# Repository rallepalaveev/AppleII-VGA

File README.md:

# Apple II VGA Card

This project is a VGA card for Apple II computers to ouput a crisp RGB signal to a
VGA monitor instead of having to rely on the composite output. This is accomplished
by snooping the 6502 bus and creating a shadow copy of the video memory within a
Raspberry Pi Pico, then processing the raw video memory contents to output a "perfect"
signal.

    +------+                +-----+      +-----------+
    | 6502 |________________| RAM |______| Composite | 
    | CPU  |  System   \    +-----+      | Video Gen |
    +------+   Bus     |                 +-----------+
                       |    +-----------+
                       \____| Raspberry |_________________\
                            |  Pi Pico  |   640x480 VGA   /
                            +-----------+

These features are currently supported:
 * Generates a 640x480@60 VGA signal with 3 bits per color channel using resistor DACs
 * Text mode (monochrome)
 * Lo-res mode with no color fringing between the chunky pixels
 * Hi-res mode with simulated NTSC artifact color
 * Mixed lo-res and hi-res modes with monochrome text and no color fringing
 * Apple IIe video modes: 80-column text, double-lores, & double-hires
   (thanks to @dkgrizzly and @Paco1979)
 * Soft-monochrome mode to force display as if on a monochrome monitor
 * Some Video-7 RGB card extended graphical modes are implemented
 * Compatibility with Videx VideoTerm modes on Apple II+ (thanks to @abaffa)
 * ProDOS [config-disk](config-disk/A2VGA_config.po?raw=true)

I had these goals in mind during design:
 * Generate video out to a more modern display - I don't have any old CRTs for
   displaying composite signals any more and composite to HDMI adapters don't work well.
 * Generate crisp video - I wanted "perfect" video output, the way that it should have
   been barring technical difficulties of displays in 1980. So like, no NTSC artifact
   coloring where it's not supposed to be.
 * Non-invasive - I didn't want to have to solder or modify my logic board.
 * Common parts - The parts to build should be cheap and easy to get anywhere,
   just like the original Apple II
 * Open-source - If this helps anyone else make their Apple II better then that's
   a bonus.

I also wanted to see if a Pi Pico could actually work on an 8-bit CPU bus, since the docs
say it should work but there were no code examples.

## Project Status

This is currently a DIY project that several folks have built on their own, ranging from
[hand-wired prototype boards](docs/prototype_card.jpg) to
[custom](https://user-images.githubusercontent.com/7944844/243266290-d05ce815-0a3d-4464-a4da-49dd44d71e92.jpg)
[PCBs](https://user-images.githubusercontent.com/94628/253134471-0d5ad359-75ae-400a-acfa-885c80c36e78.jpg)
and run in their Apple II+'s and IIe's. I consider it to be pretty stable at this point.

Included in this repo are:
 * The main expansion board [KiCad Project](AppleVGA/), [Schematics](AppleVGA/AppleVGA.pdf),
   [BOM](AppleVGA/AppleVGA_BOM.csv), and [Gerber files](AppleVGA/outputs/)
 * An optional connector board [KiCad Project](AppleVGA-Connector/),
   [Schematics](AppleVGA-Connector/AppleVGA-Connector.pdf),
   [BOM](AppleVGA-Connector/AppleVGA-Connector_BOM.csv),
   and [Gerber files](AppleVGA-Connector/outputs/). (You could also build a custom cable instead)
 * The [source code for the Pi Pico microcontroller](pico/)

If you're going to build a card then check the [assembly guide](docs/Assembly.md) and
[hardware changelog](AppleVGA/CHANGELOG.txt) for important notes.

Many thanks go to the folks in the Discussion area to help push this project forward with bug
fixes & reports, and design ideas!

**Main board**

**Connector board**
_thanks to @swetland for [this idea](https://github.com/markadev/AppleII-VGA/discussions/15#discussioncomment-6432841)_

**In the wild**

## Comparisons

Here are a few comparisons of the VGA card output vs composite video through
a cheap composite -> HDMI adapter

**Text**

**Lores**

**Hires**

**DHires**

**80 Columns**

## 80 Column support for the Apple II+

The firmware implements Videx VideoTerm compatibility when there's a VideoTerm card installed
in slot 3. It's not enabled by default but if you have a Videx VideoTerm card in slot 3
then you can enable 80 column VGA support using the Configuration Disk image. The VGA card
can still be installed in any slot.

**Apple II+ running 80 Columns Examples**

## Future work

With the Rev B hardware design, the firmware has access to the Apple bus' SYNC signal
when installed in slot 7. Theoretically the firmware could synchronize the VGA display
scans with the video hardware in the Apple II.

Though possible, it looks like it would be a large overhaul to implement this synchronization
and I've found no real-world use for it so I don't plan on completing this functionality.

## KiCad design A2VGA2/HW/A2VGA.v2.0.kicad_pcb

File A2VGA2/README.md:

This is a redesign of the Apple II VGA based on the PR2350 chip with 48 GPIOs (on Clintech Pico Board) which is 5V tolerant and hence no trinsceivers would be needed.

The A2VGA2 hardware design is released under the MIT License:

    Board design by Ralle Palaveev, Copyright (c) 2026.

    Firmware adaptation for RP2350 by Oliver Schmidt, Copyright (c) 2026.

The firmware project would be based on awesome work from the following Apple II VGA project:

    AppleII-VGA. MIT License. Copyright (c) 2021-2022 Mark Aikens.

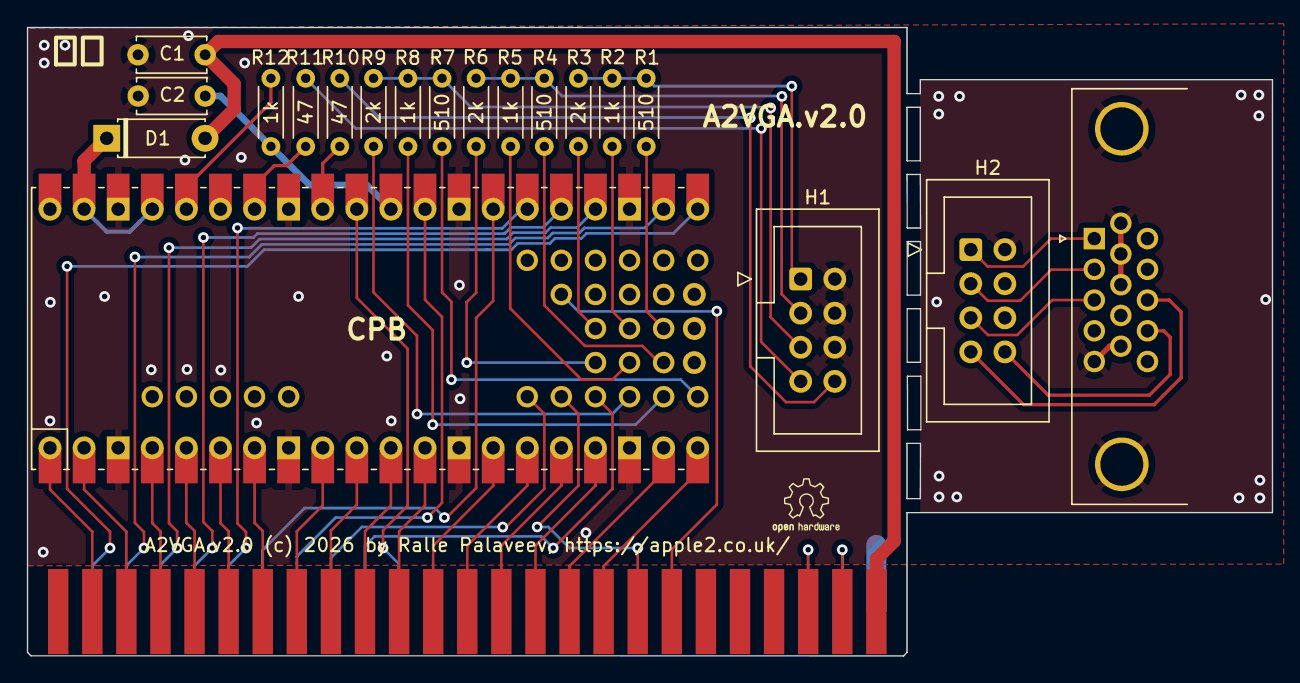
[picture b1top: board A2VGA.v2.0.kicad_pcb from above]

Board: 2 copper layers, 92.8 x 46.8 mm, 19 parts (0 on the bottom side), 21 nets.

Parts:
C1, C2: 100n; C_Disc_D5.0mm_W2.5mm_P5.00mm
D1: D_T-1_P5.08mm_Horizontal
H1, H2: IDC-Header_2x04_P2.54mm_Vertical
H3: DB15_Female_HighDensity_MountingHoles; DSUB-15-HD_Female_Horizontal_P2.29x1.98mm_EdgePinOffset3.03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
R1, R4, R7: 510; R_Axial_DIN0204_L3.6mm_D1.6mm_P5.08mm_Horizontal
R2, R5, R8, R12: 1k; R_Axial_DIN0204_L3.6mm_D1.6mm_P5.08mm_Horizontal
R3, R6, R9: 2k; R_Axial_DIN0204_L3.6mm_D1.6mm_P5.08mm_Horizontal
R10, R11: 47; R_Axial_DIN0204_L3.6mm_D1.6mm_P5.08mm_Horizontal
U1: CPB; CPB_SMD_TH

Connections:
3.3V: R12.1, U1.36
5V: C1.2, D1.2
B0: R7.2, U1.70
B1: R8.2, U1.69
B2: R9.2, U1.68
B_out: H1.5, H2.5, H3.3, R7.1, R8.1, R9.1
G0: R4.2, U1.58
G1: R5.2, U1.57
G2: R6.2, U1.56
GND: C1.1, C2.1, H1.2, H1.4, H1.6, H2.2, H2.4, H2.6, H3.0, H3.5, H3.6, H3.7, H3.8, H3.10, U1.3, U1.8, U1.13, U1.18, U1.23, U1.28, U1.33, U1.38
G_out: H1.3, H2.3, H3.2, R4.1, R5.1, R6.1
HSYNC: R11.2, U1.34
HS_out: H1.7, H2.7, H3.13, R11.1
R0: R1.2, U1.54
R1: R2.2, U1.53
R2: R3.2, U1.52
RUN: C2.2, R12.2, U1.30
R_out: H1.1, H2.1, H3.1, R1.1, R2.1, R3.1
VSYNC: R10.2, U1.32
VSYS: D1.1, U1.37, U1.39
VS_out: H1.8, H2.8, H3.14, R10.1

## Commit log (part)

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2026-06-27 Rename README(2).md to README.md
2026-06-27 Update LICENSE.md with additional copyright holders
2026-06-27 Rename LICENSE.md to LICENSE
2026-06-27 Update LICENSE file to remove old copyright notices
    Removed outdated copyright entries from LICENSE file.
2026-06-27 Adjust firmware for the recently added RP2354B based A2VGA2 board
    The RP2354B is 5v tolerant on most pins and has (actually more than) enough pins to directly connect both the A2 slot bus as well as the VGA connector. Therefore the 245 buffers aren't necessary anym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
2026-06-27 temporary hack to allow linking for all RP Pico variants
2026-06-27 Rename A2VGA_v2.1.jpeg to A2VGA.v2.1.jpeg
2026-06-29 Place config in last (known) flash sector

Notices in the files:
A2VGA2/HW/A2VGA.v2.0.kicad_pcb:
Board design by Ralle Palaveev, (c) 2026
Firmware by Oliver Schmidt, (c) 2026
Based on work by:
AppleII-VGA, Mark Aikens (c) 2021-2023
A2VGA.v2.0 (c) 2026 by Ralle Palaveev, https://apple2.co.uk
